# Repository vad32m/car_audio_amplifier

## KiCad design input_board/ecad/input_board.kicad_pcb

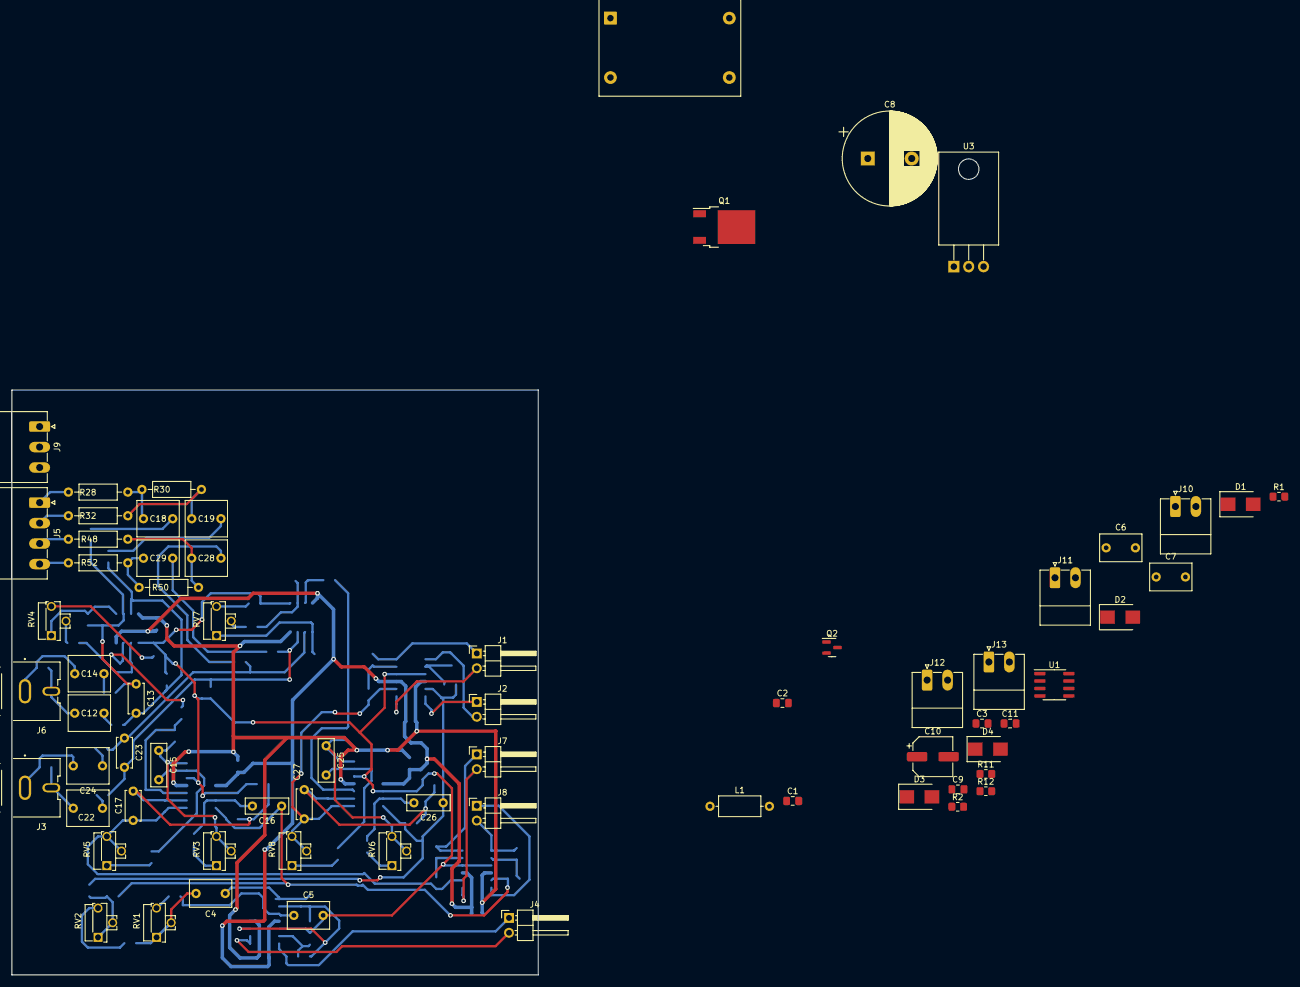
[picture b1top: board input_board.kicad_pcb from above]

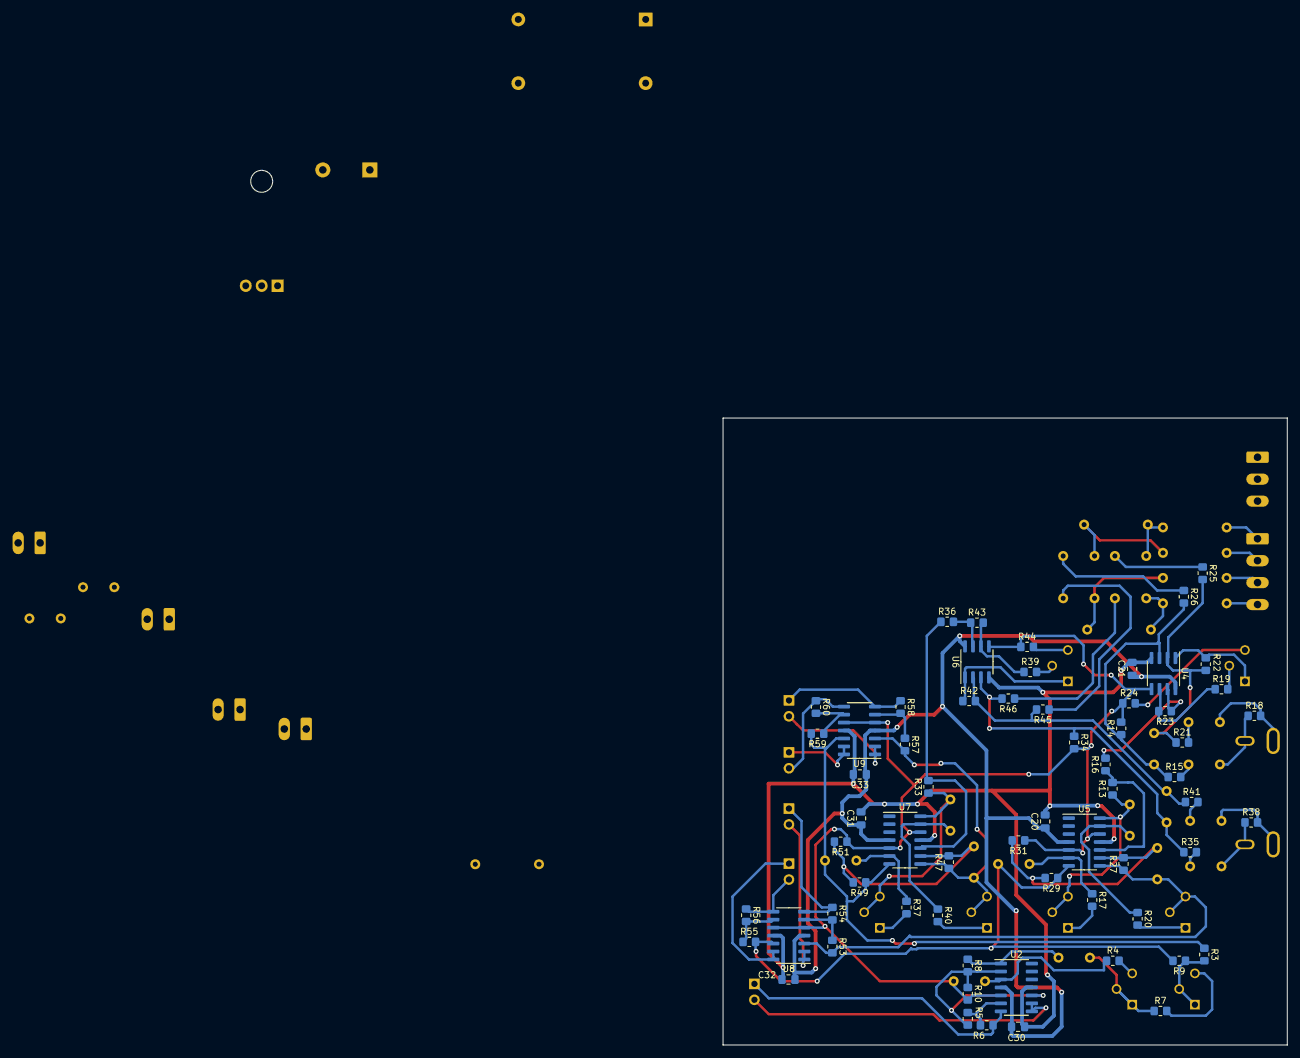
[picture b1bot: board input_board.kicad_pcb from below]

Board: 2 copper layers, 90.0 x 100.0 mm, 131 parts (63 on the bottom side), 89 nets.

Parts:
C1, C2, C3, C9, C20, C21, C30, C31, C32, C33: 100n; C_0805_2012Metric_Pad1.18x1.45mm_HandSolder
C4, C5, C6, C7: 56n; C_Rect_L7.0mm_W4.5mm_P5.00mm
C8: 1000u; CP_Radial_D16.0mm_P7.50mm
C10: 100u; CP_Elec_6.3x5.7
C11: 330n; C_0805_2012Metric_Pad1.18x1.45mm_HandSolder
C12, C14, C18, C19, C22, C24, C28, C29: 1u; C_Rect_L7.0mm_W6.0mm_P5.00mm
C13, C23: 10p; C_Disc_D5.0mm_W2.5mm_P5.00mm
C15, C16, C25, C26: 1n; C_Rect_L7.2mm_W2.5mm_P5.00mm_FKS2_FKP2_MKS2_MKP2
C17, C27: 47p; C_Disc_D5.0mm_W2.5mm_P5.00mm
D1, D2, D3, D4: SM6T18A; D_SMB
FL1: EMI_Filter_LL_1423; L_CommonMode_Toroid_Vertical_L24.0mm_W16.3mm_Px10.16mm_Py20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
J1, J2, J4, J7, J8: Conn_01x02_Female; PinHeader_1x02_P2.54mm_Horizontal
J3, J6: RCJ-041; CUI_RCJ-041
J5: Conn_01x04_Female; PhoenixContact_MC_1,5_4-G-3.5_1x04_P3.50mm_Horizontal
J9: Conn_01x03_Male; PhoenixContact_MC_1,5_3-G-3.5_1x03_P3.50mm_Horizontal
J10, J11, J12, J13: Conn_01x02_Female; PhoenixContact_MC_1,5_2-G-3.5_1x02_P3.50mm_Horizontal
L1: 10u; L_Axial_L7.0mm_D3.3mm_P10.16mm_Horizontal_Fastron_MICC
Q1: IRFR5305; TO-252-2
Q2: BC817; SOT-23
R1, R2, R3, R5, R6, R9, R10, R11, R16, R18, R27, R29, R36, R38, R47, R49, R53, R54, R55, R56, R57, R58, R59, R60: 10K; R_0805_2012Metric_Pad1.20x1.40mm_HandSolder
R4, R7: 20K; R_0805_2012Metric_Pad1.20x1.40mm_HandSolder
R8: 5.8K; R_0805_2012Metric_Pad1.20x1.40mm_HandSolder
R12, R24, R44: 4.7K; R_0805_2012Metric_Pad1.20x1.40mm_HandSolder
R13, R33: 7.5K; R_0805_2012Metric_Pad1.20x1.40mm_HandSolder
R14, R15, R17, R19, R20, R21, R22, R23, R25, R26, R31, R34, R35, R37, R39, R40, R41, R42, R43, R45, R46, R51: 30K; R_0805_2012Metric_Pad1.20x1.40mm_HandSolder
R28, R32, R48, R52: 10K; R_Axial_DIN0207_L6.3mm_D2.5mm_P10.16mm_Horizontal
R30, R50: 4.7K; R_Axial_DIN0207_L6.3mm_D2.5mm_P10.16mm_Horizontal
RV1, RV2, RV3, RV4, RV5, RV6, RV7, RV8: 50K; Potentiometer_Runtron_RM-063_Horizontal
U1: LM358; SOIC-8_3.9x4.9mm_P1.27mm
U2, U5, U7, U8, U9: MC33079; SOIC-14_3.9x8.7mm_P1.27mm
U3: L7809; TO-220-3_Horizontal_TabDown
U4, U6: NJM4580; SOIC-8_3.9x4.9mm_P1.27mm

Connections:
+9V: C1.1, C2.1, C9.1, C10.1, C20.1, C21.1, C30.1, C31.1, C32.1, C33.1, R1.1, U1.8 (V+), U2.4 (V+), U3.3 (OUT), U4.8 (V+), U5.4 (V+), U6.8 (V+), U7.4 (V+), U8.4 (V+), U9.4 (V+)
/ENABLE: D3.1 (A1), J9.3, R12.1
/GND_DIRTY: C7.2, D2.1 (A1), D4.1 (A1), FL1.1, J9.2, Q2.2 (E)
/VCC_BRFORE_STAB: C11.1, L1.2, U3.1 (IN)
/VCC_UNFILTERED: C6.1, D1.1 (A1), J9.1, Q1.3 (S), R11.2
/VCC_UNF_EN: FL1.2, Q1.2 (D)
/left_rca_g: C14.2, J6.1, R18.2
/left_rca_p: C12.2, J6.2, R18.1
/lfe_n: J4.2, U2.8, U2.9 (-)
/lfe_p: J4.1, R6.1, U2.7
/preamp_filter_l/HIGH: C17.1, R27.1, R53.2, RV5.2, RV5.3, U5.8, U8.3 (+)
/preamp_filter_l/LO_MID: C16.1, R9.2, R29.1, R55.2, U5.7, U8.12 (+)
/preamp_filter_l/hi_n: J5.1, R28.2
/preamp_filter_l/hi_p: J5.2, R32.2
/preamp_filter_l/preamp_n: C13.1, R21.1, R22.2, R25.2, U4.2 (-)
/preamp_filter_l/preamp_p: C13.2, R14.1, R15.1, R26.2, U4.3 (+)
/preamp_filter_r/HIGH: C27.1, R47.1, R57.2, RV8.2, RV8.3, U7.8, U9.3 (+)
/preamp_filter_r/LO_MID: C26.1, R3.1, R49.1, R59.2, U7.7, U9.12 (+)
/preamp_filter_r/hi_n: J5.3, R48.2
/preamp_filter_r/hi_p: J5.4, R52.2
/preamp_filter_r/preamp_n: C23.1, R41.1, R42.2, R45.2, U6.2 (-)
/preamp_filter_r/preamp_p: C23.2, R34.1, R35.1, R46.2, U6.3 (+)
/right_rca_g: C24.2, J3.1, R38.2
/right_rca_p: C22.2, J3.2, R38.1
/se_to_diff_l/HI_N: J7.2, U8.1, U8.2 (-)
/se_to_diff_l/HI_P: J7.1, R54.1, U8.7
/se_to_diff_l/LOMID_N: J8.2, R56.1, U8.8
/se_to_diff_l/LOMID_P: J8.1, U8.13 (-), U8.14
/se_to_diff_r/HI_N: J1.2, U9.1, U9.2 (-)
/se_to_diff_r/HI_P: J1.1, R58.1, U9.7
/se_to_diff_r/LOMID_N: J2.2, R60.1, U9.8
/se_to_diff_r/LOMID_P: J2.1, U9.13 (-), U9.14
GND: C1.2, C2.2, C3.2, C8.2, C9.2, C10.2, C11.2, C20.2, C21.2, C30.2, C31.2, C32.2, C33.2, FL1.4, J10.2, J11.2, J12.2, J13.2, R2.2, U1.4 (V-), U2.11 (V-), U3.2 (GND), U4.4 (V-), U5.11 (V-), U6.4 (V-), U7.11 (V-), U8.11 (V-), U9.11 (V-)
unnamed: C3.1, R1.2, R2.1, U1.3 (+)
unnamed: C4.1, R8.1, U2.1
unnamed: C4.2, R7.1, RV1.1, RV1.2
unnamed: C5.1, R4.1, U2.3 (+)
unnamed: C6.2, C7.1
unnamed: C12.1, R15.2
unnamed: C14.1, R21.2
unnamed: C15.1, R13.1, RV3.2, RV3.3, U5.14
unnamed: C15.2, R20.1, U5.13 (-)
unnamed: C16.2, R17.1, U5.6 (-)
unnamed: C17.2, R27.2, R29.2, R31.2, U5.9 (-)
unnamed: C18.1, R25.1
unnamed: C18.2, R28.1, R30.2
unnamed: C19.1, R26.1
unnamed: C19.2, R30.1, R32.1
unnamed: C22.1, R35.2
unnamed: C24.1, R41.2
unnamed: C25.1, R33.1, RV6.2, RV6.3, U7.14
unnamed: C25.2, R40.1, U7.13 (-)
unnamed: C26.2, R37.1, U7.6 (-)
unnamed: C27.2, R47.2, R49.2, R51.2, U7.9 (-)
unnamed: C28.1, R45.1
unnamed: C28.2, R48.1, R50.2
unnamed: C29.1, R46.1
unnamed: C29.2, R50.1, R52.1
unnamed: D1.2 (A2), D2.2 (A2)
unnamed: D3.2 (A2), D4.2 (A2)
unnamed: Q1.1 (G), Q2.3 (C), R11.1
unnamed: Q2.1 (B), R12.2
unnamed: R3.2, R9.1, RV2.1, RV2.2
unnamed: R4.2, RV1.3
unnamed: R5.1, R6.2, U2.6 (-)
unnamed: R7.2, RV2.3
unnamed: R5.2, R8.2, R10.1, U2.2 (-), U2.10 (+)
unnamed: R13.2, R16.1, U5.10 (+)
unnamed: R16.2, R23.1, U4.7
unnamed: R17.2, RV3.1
unnamed: R19.1, R23.2, U4.6 (-)
unnamed: R19.2, RV4.2
unnamed: R20.2, RV5.1
unnamed: R22.1, RV4.1, U4.1
unnamed: R24.2, RV4.3
unnamed: R33.2, R36.1, U7.10 (+)
unnamed: R36.2, R43.1, U6.7
unnamed: R37.2, RV6.1
unnamed: R39.1, R43.2, U6.6 (-)
unnamed: R39.2, RV7.2
unnamed: R40.2, RV8.1
unnamed: R42.1, RV7.1, U6.1
unnamed: R44.2, RV7.3
unnamed: R53.1, R54.2, U8.6 (-)
unnamed: R55.1, R56.2, U8.9 (-)
unnamed: R57.1, R58.2, U9.6 (-)
unnamed: R59.1, R60.2, U9.9 (-)
half_vcc: C5.2, R10.2, R14.2, R24.1, R31.1, R34.2, R44.1, R51.1, U1.1, U1.2 (-), U2.5 (+), U4.5 (+), U5.5 (+), U5.12 (+), U6.5 (+), U7.5 (+), U7.12 (+), U8.5 (+), U8.10 (+), U9.5 (+), U9.10 (+)
vcc_prefiltered: C8.1, FL1.3, J10.1, J11.1, J12.1, J13.1, L1.1

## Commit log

2021-10-09 Inout board: add files for simu;ation of input board
2021-10-09 Input board: add initial kicad schematic
2021-12-26 Input board: simplify input filtering
2021-12-26 Input board: migrate to KiCAD 6.0
2021-12-29 Input board: fix scematic and initial version of layout
